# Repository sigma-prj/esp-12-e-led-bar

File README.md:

ESP-12E \ ESP-12F LED Bar PCB Design
==============

This repository contains sample PCB design representing LED Bar with integration of ESP-12E\ESP-12F module.
This LED Bar can be used for various purposes to indicate different values like temperature, humidity, highway traffic congestion, etc.
Solution is based on SN74HC595 shift register allowing to allocate just 3 ESP module pins to control 8 LEDs.
PCB is powered by standard micro-USB connector 5V rail. It is converted further to 3.3 V using AMS1117-3.3 module to power ESP module.

Requirements and Dependencies
-----------------------------

Project is built using KiCad version 5.1.9

Schema Design
-----------------------------

ESP8266 module has quite limited amount of GPIO output pins which could be used to control set of LEDs. To overcome this problem we can use Shift Register 74HC595 chip which can play a role of serial to parallel converter. This way, we can allocate just 3 pins from ESP module to control any amount of LED - as 74HC595 Shift Registers can be cascaded into array using QH' pin. Under current design there is need to control just 8 LEDs, so one single 74HC595 register should be sufficient for these purposes.

The following connection schema is used to drive 8 LEDs:

In case of application needs to be flashed into ESP chip - the corresponding GPIO 0 pin needs to be pulled down
and in order to run application this pin needs to be pulled up.
Switch between GPIO 0 'pull up' and 'pull down' state can be done using single jumper placed to JMPR_EXEC either to JMPR_FLASH connector.

The main purpose to drive LEDs on a separate 5V rail - to do not put extra load on AMS1117-3.3 module. Also green LEDs do have quite large voltage drop which can be more than 2V. In case of LEDs will be driven by 3.3V then slight difference in LEDs voltage drop can have increased current value deviation from expected value (hence deviation in brightness). This happens when the same value is used for all current limiting resistors. Driving LEDs by 5V rail will make this deviation negligible.

This schema also has some room for optimization as amount of NPN transistors can be reduced from 8 to 3 which currently are used as a voltage level shift from 3.3V to 5V to drive LEDs. New PCBs revisions would include this change, but for now it can be kept for you to optimize as a practice exercise.

Sample ESP8266 Application for PCB Testing
-----------------------------

Once schema is assembled the following sample application can be used to test PCB.
This will try to ignite all LEDs sequentially, one-by-one.
This way, the application below can show whether Shift register is operating properly.

```c++

#include <osapi.h>
#include <user_interface.h>
#include <gpio.h>

#define LED_COUNT        8

#define SYSTEM_PARTITION_RF_CAL_SZ    0x1000
#define SYSTEM_PARTITION_PHY_DATA_SZ   0x1000
#define SYSTEM_PARTITION_SYSTEM_PARAMETER_SZ 0x3000
#define SYSTEM_SPI_SIZE       0x400000
#define SYSTEM_PARTITION_RF_CAL_ADDR   0x3FB000
#define SYSTEM_PARTITION_PHY_DATA_ADDR   0x3FC000
#define SYSTEM_PARTITION_SYSTEM_PARAMETER_ADDR 0x3FE000

// ESP pin connected to Shift Register 'SERIAL DATA' line
static const uint16 GPIO_PIN_SER_DATA = 4;
// ESP pin connected to Shift Register 'SERIAL CLOCK' line
static const uint16 GPIO_PIN_SER_CLOCK = 5;
// ESP pin connected to Shift Register 'READ LATCH' line
static const uint16 GPIO_PIN_READ_LATCH = 12;
// ESP internal LED pin number
static const uint16 GPIO_PIN_LED  = 2;

static const uint32 TIMER_IDX_RESET  = 1000000000;

// Delay in microseconds between Shift Register clock signals
static const uint16 DELAY_SHIFT_REG  = 50;

// This timer is used to update LED bar status
static os_timer_t start_timer;
// Initial timer tick value
static uint32 tick_index = 0L;

static const partition_item_t part_table[] =
{
 { SYSTEM_PARTITION_RF_CAL,    SYSTEM_PARTITION_RF_CAL_ADDR,   SYSTEM_PARTITION_RF_CAL_SZ    },
 { SYSTEM_PARTITION_PHY_DATA,   SYSTEM_PARTITION_PHY_DATA_ADDR,   SYSTEM_PARTITION_PHY_DATA_SZ   },
 { SYSTEM_PARTITION_SYSTEM_PARAMETER, SYSTEM_PARTITION_SYSTEM_PARAMETER_ADDR, SYSTEM_PARTITION_SYSTEM_PARAMETER_SZ }
};

// ############################# LED BAR - DISPLAY LEVEL  #############################

static void show_level(uint16 level)
{
 uint16 i;
 for (i = 0; i < LED_COUNT; ++i)
 {
  GPIO_OUTPUT_SET(GPIO_PIN_SER_DATA, (i < level));
  os_delay_us(DELAY_SHIFT_REG);
  GPIO_OUTPUT_SET(GPIO_PIN_SER_CLOCK, 1);
  os_delay_us(DELAY_SHIFT_REG);
  GPIO_OUTPUT_SET(GPIO_PIN_SER_CLOCK, 0);
  os_delay_us(DELAY_SHIFT_REG);
 }
 GPIO_OUTPUT_SET(GPIO_PIN_READ_LATCH, 1);
 os_delay_us(DELAY_SHIFT_REG);
 GPIO_OUTPUT_SET(GPIO_PIN_READ_LATCH, 0);
 os_delay_us(DELAY_SHIFT_REG);
}

// ################ APPLICATION MAIN LOOP METHOD (TRIGGERED EACH SECOND) ################

void main_timer_handler(void* arg)
{
 show_level(tick_index % (LED_COUNT + 1));
 ++tick_index;
 if (tick_index >= TIMER_IDX_RESET)
 {
  tick_index = 0;
 }
}

// ####################### APPLICATION MAIN INIT METHODS ################################

void ICACHE_FLASH_ATTR user_pre_init(void)
{
 system_partition_table_regist(part_table, 3, SPI_FLASH_SIZE_MAP);
}

void on_user_init_completed(void)
{
 // Timer setup to trigger each second
 os_timer_setfn(&start_timer, (os_timer_func_t*)main_timer_handler, NULL);
 os_timer_arm(&start_timer, 1000, 1);
}

void ICACHE_FLASH_ATTR user_init(void)
{
 gpio_init();
 // ESP pin modes initialization
 PIN_FUNC_SELECT(PERIPHS_IO_MUX_GPIO2_U, FUNC_GPIO2);
 PIN_FUNC_SELECT(PERIPHS_IO_MUX_GPIO4_U, FUNC_GPIO4);
 PIN_FUNC_SELECT(PERIPHS_IO_MUX_GPIO5_U, FUNC_GPIO5);
 PIN_FUNC_SELECT(PERIPHS_IO_MUX_MTDI_U, FUNC_GPIO12);
 // ESP pin values initialization
 GPIO_OUTPUT_SET(GPIO_PIN_LED, 0);
 GPIO_OUTPUT_SET(GPIO_PIN_SER_DATA, 0);
 GPIO_OUTPUT_SET(GPIO_PIN_SER_CLOCK, 0);
 GPIO_OUTPUT_SET(GPIO_PIN_READ_LATCH, 0);
 system_init_done_cb(on_user_init_completed);
}

```

License
-----------------------------

ESP-12E \ ESP-12F LED Bar PCB Design by www.sigmaprj.com

Creative Commons 4.0 (BY 4.0)

```
Attribution 4.0 International

=======================================================================

Creative Commons Corporation ("Creative Commons") is not a law firm and
does not provide legal services or legal advice. Distribution of
Creative Commons public licenses does not create a lawyer-client or
other relationship. Creative Commons makes its licenses and related
information available on an "as-is" basis. Creative Commons gives no
warranties regarding its licenses, any material licensed under their
terms and conditions, or any related information. Creative Commons
disclaims all liability for damages resulting from their use to the
fullest extent possible.

Using Creative Commons Public Licenses

Creative Commons public licenses provide a standard set of terms and
conditions that creators and other rights holders may use to share
original works of authorship and other material subject to copyright
and certain other rights specified in the public license below. The
following considerations are for informational purposes only, are not
exhaustive, and do not form part of our licenses.

     Considerations for licensors: Our public licenses are
     intended for use by those authorized to give the public
     permission to use material in ways otherwise restricted by
     copyright and certain other rights. Our licenses are
     irrevocable. Licensors should read and understand the terms
     and conditions of the license they choose before applying it.
     Licensors should also secure all rights necessary before
     applying our licenses so that the public can reuse the
     material as expected. Licensors should clearly mark any
     material not subject to the license. This includes other CC-
     licensed material, or material used under an exception or
     limitation to copyright. More considerations for licensors:
    wiki.creativecommons.org/Considerations_for_licensors

     Considerations for the public: By using one of our public
     licenses, a licensor grants the public permission to use the
     licensed material under specified terms and conditions. If
     the licensor's permission is not necessary for any reason--for
     example, because of any applicable exception or limitation to
     copyright--then that use is not regulated by the license. Our
     licenses grant only permissions under copyright and certain
     other rights that a licensor has authority to grant. Use of
     the licensed material may still be restricted for other
     reasons, including because others have copyright or other
     rights in the material. A licensor may make special requests,
     such as asking that all changes be marked or described.
     Although not required by our licenses, you are encouraged to
     respect those requests where reasonable. More considerations
     for the public:
    wiki.creativecommons.org/Considerations_for_licensees

=======================================================================

Creative Commons Attribution 4.0 International Public License

By exercising the Licensed Rights (defined below), You accept and agree
to be bound by the terms and conditions of this Creative Commons
Attribution 4.0 International Public License ("Public License"). To the
extent this Public License may be interpreted as a contract, You are
granted the Licensed Rights in consideration of Your acceptance of
these terms and conditions, and the Licensor grants You such rights in
consideration of benefits the Licensor receives from making the
Licensed Material available under these terms and conditions.

Section 1 -- Definitions.

  a. Adapted Material means material subject to Copyright and Similar
     Rights that is derived from or based upon the Licensed Material
     and in which the Licensed Material is translated, altered,
     arranged, transformed, or otherwise modified in a manner requiring
     permission under the Copyright and Similar Rights held by the
     Licensor. For purposes of this Public License, where the Licensed
     Material is a musical work, performance, or sound recording,
     Adapted Material is always produced where the Licensed Material is
     synched in timed relation with a moving image.

  b. Adapter's License means the license You apply to Your Copyright
     and Similar Rights in Your contributions to Adapted Material in
     accordance with the terms and conditions of this Public License.

  c. Copyright and Similar Rights means copyright and/or similar rights
     closely related to copyright including, without limitation,
     performance, broadcast, sound recording, and Sui Generis Database
     Rights, without regard to how the rights are labeled or
     categorized. For purposes of this Public License, the rights
     specified in Section 2(b)(1)-(2) are not Copyright and Similar
     Rights.

  d. Effective Technological Measures means those measures that, in the
     absence of proper authority, may not be circumvented under laws
     fulfilling obligations under Article 11 of the WIPO Copyright
     Treaty adopted on December 20, 1996, and/or similar international
     agreements.

  e. Exceptions and Limitations means fair use, fair dealing, and/or
     any other exception or limitation to Copyright and Similar Rights
     that applies to Your use of the Licensed Material.

  f. Licensed Material means the artistic or literary work, database,
     or other material to which the Licensor applied this Public
     License.

  g. Licensed Rights means the rights granted to You subject to the
     terms and conditions of this Public License, which are limited to
     all Copyright and Similar Rights that apply to Your use of the
     Licensed Material and that the Licensor has authority to license.

  h. Licensor means the individual(s) or entity(ies) granting rights
     under this Public License.

  i. Share means to provide material to the public by any means or
     process that requires permission under the Licensed Rights, such
     as reproduction, public display, public performance, distribution,
     dissemination, communication, or importation, and to make material
     available to the public including in ways that members of the
     public may access the material from a place and at a time
     individually chosen by them.

  j. Sui Generis Database Rights means rights other than copyright
     resulting from Directive 96/9/EC of the European Parliament and of
     the Council of 11 March 1996 on the legal protection of databases,
     as amended and/or succeeded, as well as other essentially
     equivalent rights anywhere in the world.

  k. You means the individual or entity exercising the Licensed Rights
     under this Public License. Your has a corresponding meaning.

Section 2 -- Scope.

  a. License grant.

       1. Subject to the terms and conditions of this Public License,
          the Licensor hereby grants You a worldwide, royalty-free,
          non-sublicensable, non-exclusive, irrevocable license to
          exercise the Licensed Rights in the Licensed Material to:

            a. reproduce and Share the Licensed Material, in whole or
               in part; and

            b. produce, reproduce, and Share Adapted Material.

       2. Exceptions and Limitations. For the avoidance of doubt, where
          Exceptions and Limitations apply to Your use, this Public
          License does not apply, and You do not need to comply with
          its terms and conditions.

       3. Term. The term of this Public License is specified in Section
          6(a).

       4. Media and formats; technical modifications allowed. The
          Licensor authorizes You to exercise the Licensed Rights in
          all media and formats whether now known or hereafter created,
          and to make technical modifications necessary to do so. The
          Licensor waives and/or agrees not to assert any right or
          authority to forbid You from making technical modifications
          necessary to exercise the Licensed Rights, including
          technical modifications necessary to circumvent Effective
          Technological Measures. For purposes of this Public License,
          simply making modifications authorized by this Section 2(a)
          (4) never produces Adapted Material.

       5. Downstream recipients.

            a. Offer from the Licensor -- Licensed Material. Every
               recipient of the Licensed Material automatically
               receives an offer from the Licensor to exercise the
               Licensed Rights under the terms and conditions of this
               Public License.

            b. No downstream restrictions. You may not offer or impose
               any additional or different terms or conditions on, or
               apply any Effective Technological Measures to, the
               Licensed Material if doing so restricts exercise of the
               Licensed Rights by any recipient of the Licensed
               Material.

       6. No endorsement. Nothing in this Public License constitutes or
          may be construed as permission to assert or imply that You
          are, or that Your use of the Licensed Material is, connected
          with, or sponsored, endorsed, or granted official status by,
          the Licensor or others designated to receive attribution as
          provided in Section 3(a)(1)(A)(i).

  b. Other rights.

       1. Moral rights, such as the right of integrity, are not
          licensed under this Public License, nor are publicity,
          privacy, and/or other similar personality rights; however, to
          the extent possible, the Licensor waives and/or agrees not to
          assert any such rights held by the Licensor to the limited
          extent necessary to allow You to exercise the Licensed
          Rights, but not otherwise.

       2. Patent and trademark rights are not licensed under this
          Public License.

       3. To the extent possible, the Licensor waives any right to
          collect royalties from You for the exercise of the Licensed
          Rights, whether directly or through a collecting society
          under any voluntary or waivable statutory or compulsory
          licensing scheme. In all other cases the Licensor expressly
          reserves any right to collect such royalties.

Section 3 -- License Conditions.

Your exercise of the Licensed Rights is expressly made subject to the
following conditions.

  a. Attribution.

       1. If You Share the Licensed Material (including in modified
          form), You must:

            a. retain the following if it is supplied by the Licensor
               with the Licensed Material:

                 i. identification of the creator(s) of the Licensed
                    Material and any others designated to receive
                    attribution, in any reasonable manner requested by
                    the Licensor (including by pseudonym if
                    designated);

                ii. a copyright notice;

               iii. a notice that refers to this Public License;

                iv. a notice that refers to the disclaimer of
                    warranties;

                 v. a URI or hyperlink to the Licensed Material to the
                    extent reasonably practicable;

            b. indicate if You modified the Licensed Material and
               retain an indication of any previous modifications; and

            c. indicate the Licensed Material is licensed under this
               Public License, and include the text of, or the URI or
               hyperlink to, this Public License.

       2. You may satisfy the conditions in Section 3(a)(1) in any
          reasonable manner based on the medium, means, and context in
          which You Share the Licensed Material. For example, it may be
          reasonable to satisfy the conditions by providing a URI or
          hyperlink to a resource that includes the required
          information.

       3. If requested by the Licensor, You must remove any of the
          information required by Section 3(a)(1)(A) to the extent
          reasonably practicable.

       4. If You Share Adapted Material You produce, the Adapter's
          License You apply must not prevent recipients of the Adapted
          Material from complying with this Public License.

Section 4 -- Sui Generis Database Rights.

Where the Licensed Rights include Sui Generis Database Rights that
apply to Your use of the Licensed Material:

  a. for the avoidance of doubt, Section 2(a)(1) grants You the right
     to extract, reuse, reproduce, and Share all or a substantial
     portion of the contents of the database;

  b. if You include all or a substantial portion of the database
     contents in a database in which You have Sui Generis Database
     Rights, then the database in which You have Sui Generis Database
     Rights (but not its individual contents) is Adapted Material; and

  c. You must comply with the conditions in Section 3(a) if You Share
     all or a substantial portion of the contents of the database.

For the avoidance of doubt, this Section 4 supplements and does not
replace Your obligations under this Public License where the Licensed
Rights include other Copyright and Similar Rights.

Section 5 -- Disclaimer of Warranties and Limitation of Liability.

  a. UNLESS OTHERWISE SEPARATELY UNDERTAKEN BY THE LICENSOR, TO THE
     EXTENT POSSIBLE, THE LICENSOR OFFERS THE LICENSED MATERIAL AS-IS
     AND AS-AVAILABLE, AND MAKES NO REPRESENTATIONS OR WARRANTIES OF
     ANY KIND CONCERNING THE LICENSED MATERIAL, WHETHER EXPRESS,
     IMPLIED, STATUTORY, OR OTHER. THIS INCLUDES, WITHOUT LIMITATION,
     WARRANTIES OF TITLE, MERCHANTABILITY, FITNESS FOR A PARTICULAR
     PURPOSE, NON-INFRINGEMENT, ABSENCE OF LATENT OR OTHER DEFECTS,
     ACCURACY, OR THE PRESENCE OR ABSENCE OF ERRORS, WHETHER OR NOT
     KNOWN OR DISCOVERABLE. WHERE DISCLAIMERS OF WARRANTIES ARE NOT
     ALLOWED IN FULL OR IN PART, THIS DISCLAIMER MAY NOT APPLY TO YOU.

  b. TO THE EXTENT POSSIBLE, IN NO EVENT WILL THE LICENSOR BE LIABLE
     TO YOU ON ANY LEGAL THEORY (INCLUDING, WITHOUT LIMITATION,
     NEGLIGENCE) OR OTHERWISE FOR ANY DIRECT, SPECIAL, INDIRECT,
     INCIDENTAL, CONSEQUENTIAL, PUNITIVE, EXEMPLARY, OR OTHER LOSSES,
     COSTS, EXPENSES, OR DAMAGES ARISING OUT OF THIS PUBLIC LICENSE OR
     USE OF THE LICENSED MATERIAL, EVEN IF THE LICENSOR HAS BEEN
     ADVISED OF THE POSSIBILITY OF SUCH LOSSES, COSTS, EXPENSES, OR
     DAMAGES. WHERE A LIMITATION OF LIABILITY IS NOT ALLOWED IN FULL OR
     IN PART, THIS LIMITATION MAY NOT APPLY TO YOU.

  c. The disclaimer of warranties and limitation of liability provided
     above shall be interpreted in a manner that, to the extent
     possible, most closely approximates an absolute disclaimer and
     waiver of all liability.

Section 6 -- Term and Termination.

  a. This Public License applies for the term of the Copyright and
     Similar Rights licensed here. However, if You fail to comply with
     this Public License, then Your rights under this Public License
     terminate automatically.

  b. Where Your right to use the Licensed Material has terminated under
     Section 6(a), it reinstates:

       1. automatically as of the date the violation is cured, provided
          it is cured within 30 days of Your discovery of the
          violation; or

       2. upon express reinstatement by the Licensor.

     For the avoidance of doubt, this Section 6(b) does not affect any
     right the Licensor may have to seek remedies for Your violations
     of this Public License.

  c. For the avoidance of doubt, the Licensor may also offer the
     Licensed Material under separate terms or conditions or stop
     distributing the Licensed Material at any time; however, doing so
     will not terminate this Public License.

  d. Sections 1, 5, 6, 7, and 8 survive termination of this Public
     License.

Section 7 -- Other Terms and Conditions.

  a. The Licensor shall not be bound by any additional or different
     terms or conditions communicated by You unless expressly agreed.

  b. Any arrangements, understandings, or agreements regarding the
     Licensed Material not stated herein are separate from and
     independent of the terms and conditions of this Public License.

Section 8 -- Interpretation.

  a. For the avoidance of doubt, this Public License does not, and
     shall not be interpreted to, reduce, limit, restrict, or impose
     conditions on any use of the Licensed Material that could lawfully
     be made without permission under this Public License.

  b. To the extent possible, if any provision of this Public License is
     deemed unenforceable, it shall be automatically reformed to the
     minimum extent necessary to make it enforceable. If the provision
     cannot be reformed, it shall be severed from this Public License
     without affecting the enforceability of the remaining terms and
     conditions.

  c. No term or condition of this Public License will be waived and no
     failure to comply consented to unless expressly agreed to by the
     Licensor.

  d. Nothing in this Public License constitutes or may be interpreted
     as a limitation upon, or waiver of, any privileges and immunities
     that apply to the Licensor or You, including from the legal
     processes of any jurisdiction or authority.

=======================================================================

Creative Commons is not a party to its public
licenses. Notwithstanding, Creative Commons may elect to apply one of
its public licenses to material it publishes and in those instances
will be considered the Licensor. The text of the Creative Commons
public licenses is dedicated to the public domain under the CC0 Public
Domain Dedication. Except for the limited purpose of indicating that
material is shared under a Creative Commons public license or as
otherwise permitted by the Creative Commons policies published at
creativecommons.org/policies, Creative Commons does not authorize the
use of the trademark "Creative Commons" or any other trademark or logo
of Creative Commons without its prior written consent including,
without limitation, in connection with any unauthorized modifications
to any of its public licenses or any other arrangements,
understandings, or agreements concerning use of licensed material. For
the avoidance of doubt, this paragraph does not form part of the
public licenses.

Creative Commons may be contacted at creativecommons.org.
```

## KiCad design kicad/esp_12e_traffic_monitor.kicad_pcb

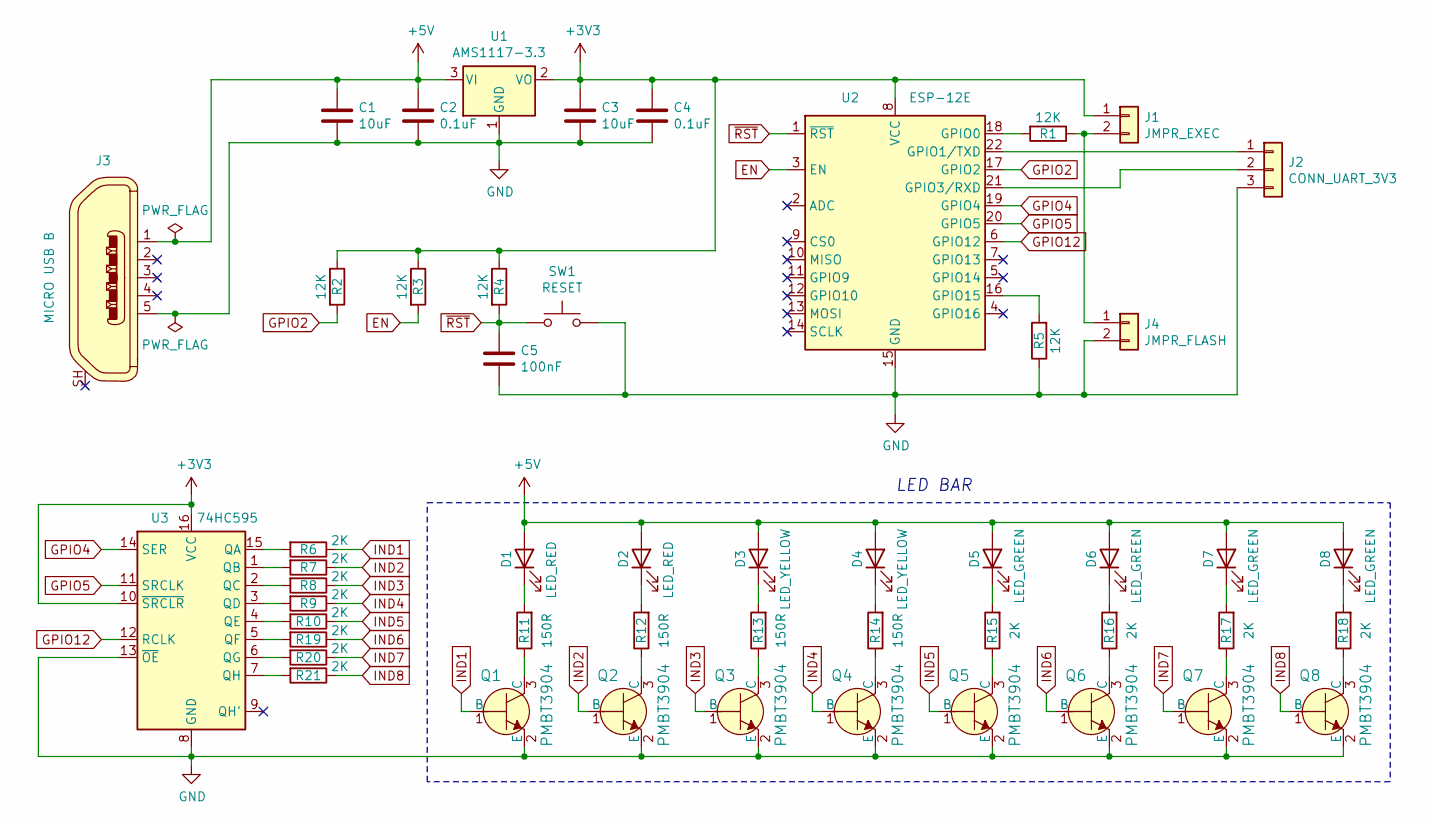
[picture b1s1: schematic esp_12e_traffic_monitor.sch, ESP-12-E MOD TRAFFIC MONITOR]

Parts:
C1, C3: 10uF; C_0603_1608Metric_Pad1.08x0.95mm_HandSolder
C2, C4: 0.1uF; C_0603_1608Metric_Pad1.08x0.95mm_HandSolder
C5: 100nF; C_0603_1608Metric_Pad1.08x0.95mm_HandSolder
D1, D2: LED_RED; LED_1206_3216Metric_Pad1.42x1.75mm_HandSolder
D3, D4: LED_YELLOW; LED_1206_3216Metric_Pad1.42x1.75mm_HandSolder
D5, D6, D7, D8: LED_GREEN; LED_1206_3216Metric_Pad1.42x1.75mm_HandSolder
J1: JMPR_EXEC; PinHeader_1x02_P2.54mm_Vertical
J2: CONN_UART_3V3; PinHeader_1x03_P2.54mm_Vertical
J3: MICRO USB B; USB_Micro-B_Custom; MPN 1050170001; Digi-Key_PN WM1399CT-ND
J4: JMPR_FLASH; PinHeader_1x02_P2.54mm_Vertical
Q1, Q2, Q3, Q4, Q5, Q6, Q7, Q8: PMBT3904; SOT-23-3; MPN PMBT3904,215
R1, R2, R3, R4, R5: 12K; R_0603_1608Metric_Pad0.98x0.95mm_HandSolder
R6, R7, R8, R9, R10, R15, R16, R17, R18, R19, R20, R21: 2K; R_0603_1608Metric_Pad0.98x0.95mm_HandSolder
R11, R12, R13, R14: 150R; R_0603_1608Metric_Pad0.98x0.95mm_HandSolder
SW1: RESET; SW_PUSH-12mm
U1: AMS1117-3.3; SOT-223-3_TabPin2
U2: ESP-12E
U3: 74HC595; SOIC-16_W3.90mm

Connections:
+3V3: C3.1, C4.1, J1.1, R2.1, R3.1, R4.1, U1.2 (VO), U2.8 (VCC), U3.10 (~SRCLR), U3.16 (VCC)
+5V: C1.1, C2.1, D1.2 (A), D2.2 (A), D3.2 (A), D4.2 (A), D5.2 (A), D6.2 (A), D7.2 (A), D8.2 (A), J3.1, U1.3 (VI)
EN: R3.2, U2.3 (EN)
GND: C1.2, C2.2, C3.2, C4.2, C5.2, J2.3, J3.5, J4.2, Q1.2 (E), Q2.2 (E), Q3.2 (E), Q4.2 (E), Q5.2 (E), Q6.2 (E), Q7.2 (E), Q8.2 (E), R5.1, SW1.2, U1.1 (GND), U2.15 (GND), U3.8 (GND), U3.13 (~OE)
GPIO2: R2.2, U2.17 (GPIO2)
GPIO4: U2.19 (GPIO4), U3.14 (SER)
GPIO5: U2.20 (GPIO5), U3.11 (SRCLK)
GPIO12: U2.6 (GPIO12), U3.12 (RCLK)
IND1: Q1.1 (B), R6.1
IND2: Q2.1 (B), R7.1
IND3: Q3.1 (B), R8.1
IND4: Q4.1 (B), R9.1
IND5: Q5.1 (B), R10.1
IND6: Q6.1 (B), R19.1
IND7: Q7.1 (B), R20.1
IND8: Q8.1 (B), R21.1
unnamed: D1.1 (K), R11.2
unnamed: D2.1 (K), R12.2
unnamed: D3.1 (K), R13.2
unnamed: D4.1 (K), R14.2
unnamed: D5.1 (K), R15.2
unnamed: D6.1 (K), R16.2
unnamed: D7.1 (K), R17.2
unnamed: D8.1 (K), R18.2
unnamed: J1.2, J4.1, R1.1
unnamed: J2.1, U2.22 (GPIO1/TXD)
unnamed: J2.2, U2.21 (GPIO3/RXD)
unnamed: Q1.3 (C), R11.1
unnamed: Q2.3 (C), R12.1
unnamed: Q3.3 (C), R13.1
unnamed: Q4.3 (C), R14.1
unnamed: Q5.3 (C), R15.1
unnamed: Q6.3 (C), R16.1
unnamed: Q7.3 (C), R17.1
unnamed: Q8.3 (C), R18.1
unnamed: R1.2, U2.18 (GPIO0)
unnamed: R5.2, U2.16 (GPIO15)
unnamed: R6.2, U3.15 (QA)
unnamed: R7.2, U3.1 (QB)
unnamed: R8.2, U3.2 (QC)
unnamed: R9.2, U3.3 (QD)
unnamed: R10.2, U3.4 (QE)
unnamed: R19.2, U3.5 (QF)
unnamed: R20.2, U3.6 (QG)
unnamed: R21.2, U3.7 (QH)
~RST: C5.1, R4.2, SW1.1, U2.1 (~RST)

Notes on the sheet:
LED BAR

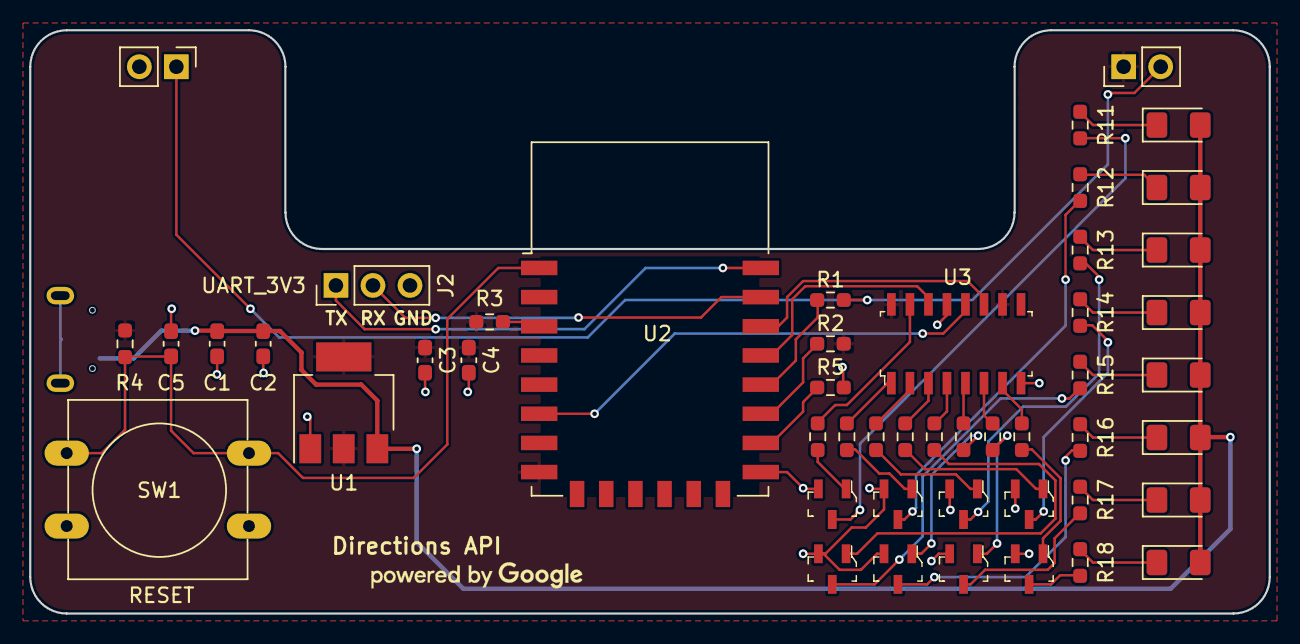
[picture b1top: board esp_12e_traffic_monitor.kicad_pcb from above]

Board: 2 copper layers, 85.0 x 40.0 mm, 50 parts (1 on the bottom side), 46 nets.

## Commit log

2022-07-05 CC 4.0 License file
2022-07-05 README file includes testing application sample
2022-07-07 Update README.md file

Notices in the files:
README.md:
iii. a notice that refers to this Public License;
c. indicate the Licensed Material is licensed under this
Public License, and include the text of, or the URI or
hyperlink to, this Public License.
Material from complying with this Public License.
replace Your obligations under this Public License where the Licensed
COSTS, EXPENSES, OR DAMAGES ARISING OUT OF THIS PUBLIC LICENSE OR
a. This Public License applies for the term of the Copyright and
this Public License, then Your rights under this Public License
will not terminate this Public License.
